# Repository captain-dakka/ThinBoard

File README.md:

# ThinBoard
A thin, low-profile mechnical keyboard. Uses Kailh Choc switches.

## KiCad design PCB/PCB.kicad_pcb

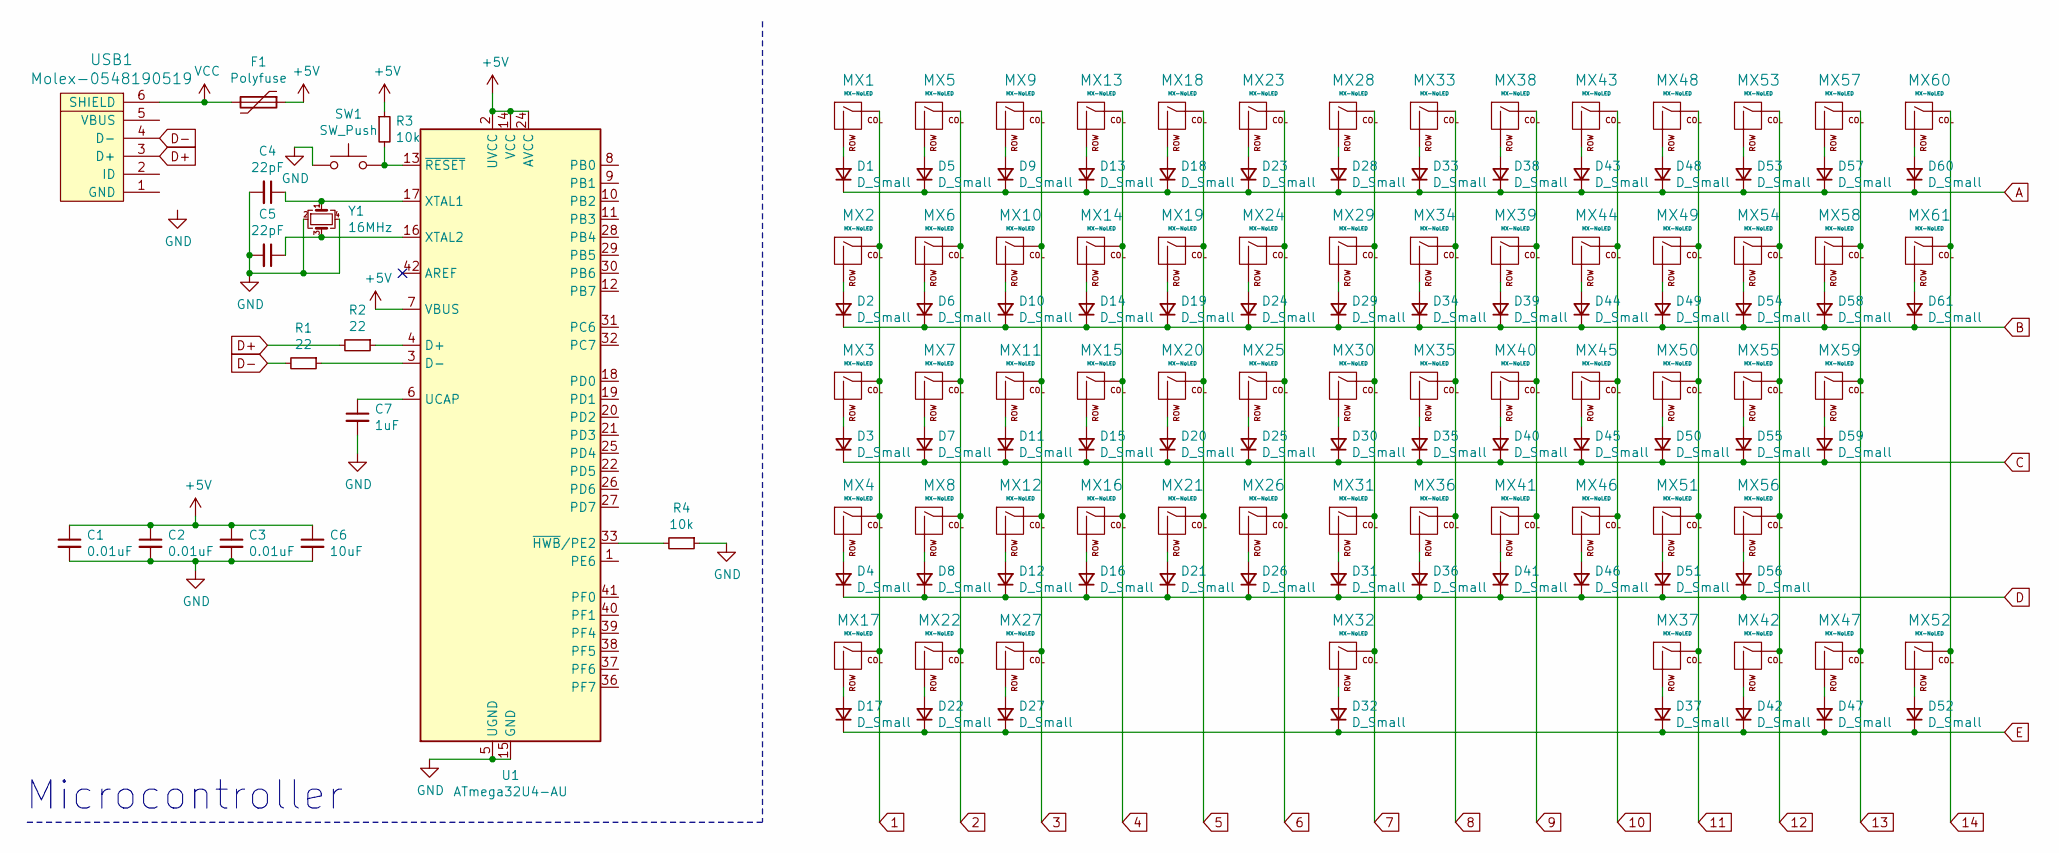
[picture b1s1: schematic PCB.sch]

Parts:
C1, C2, C3: 0.01uF; C_0805_2012Metric
C4, C5: 22pF; C_0805_2012Metric
C6: 10uF; C_0805_2012Metric
C7: 1uF; C_0805_2012Metric
D1, D2, D3, D4, D5, D6, D7, D8, D9, D10, D11, D12, D13, D14, D15, D16, D17, D18, D19, D20, D21, D22, D23, D24, D25, D26, D27, D28, D29, D30, D31, D32, D33, D34, D35, D36, D37, D38, D39, D40, D41, D42, D43, D44, D45, D46, D47, D48, D49, D50, D51, D52, D53, D54, D55, D56, D57, D58, D59, D60, D61: D_Small; D_SOD-123
F1: Polyfuse; Fuse_1206_3216Metric
MX1, MX5, MX6, MX7, MX8, MX9, MX10, MX11, MX12, MX13, MX14, MX15, MX16, MX18, MX19, MX20, MX21, MX23, MX24, MX25, MX26, MX28, MX29, MX30, MX31, MX33, MX34, MX35, MX36, MX38, MX39, MX40, MX41, MX43, MX44, MX45, MX46, MX48, MX49, MX50, MX51, MX53, MX54, MX55, MX57, MX58: MX-NoLED; SW_Kailh_Choc_V1_1.00u
MX2, MX61: MX-NoLED; SW_Kailh_Choc_V1_1.50u
MX3: MX-NoLED; SW_Kailh_Choc_V1_1.75u
MX4, MX59: MX-NoLED; SW_Kailh_Choc_V1_2.25u
MX17, MX22, MX27, MX37, MX42, MX47, MX52: MX-NoLED; SW_Kailh_Choc_V1_1.25u
MX32: MX-NoLED; SW_Kailh_Choc_V1_6.25u
MX56: MX-NoLED; SW_Kailh_Choc_V1_2.75u
MX60: MX-NoLED; SW_Kailh_Choc_V1_2.00u
R1, R2: 22; R_0805_2012Metric
R3, R4: 10k; R_0805_2012Metric
SW1: SW_Push; SKQG-1155865
U1: ATmega32U4-AU; TQFP-44_10x10mm_P0.8mm
USB1: Molex-0548190519; Molex-0548190589
Y1: 16MHz; Crystal_SMD_3225-4Pin_3.2x2.5mm

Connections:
1: MX1.1 (COL), MX2.1 (COL), MX3.1 (COL), MX4.1 (COL), MX17.1 (COL)
2: MX5.1 (COL), MX6.1 (COL), MX7.1 (COL), MX8.1 (COL), MX22.1 (COL)
3: MX9.1 (COL), MX10.1 (COL), MX11.1 (COL), MX12.1 (COL), MX27.1 (COL)
4: MX13.1 (COL), MX14.1 (COL), MX15.1 (COL), MX16.1 (COL)
5: MX18.1 (COL), MX19.1 (COL), MX20.1 (COL), MX21.1 (COL)
6: MX23.1 (COL), MX24.1 (COL), MX25.1 (COL), MX26.1 (COL)
7: MX28.1 (COL), MX29.1 (COL), MX30.1 (COL), MX31.1 (COL), MX32.1 (COL)
8: MX33.1 (COL), MX34.1 (COL), MX35.1 (COL), MX36.1 (COL)
9: MX38.1 (COL), MX39.1 (COL), MX40.1 (COL), MX41.1 (COL)
10: MX43.1 (COL), MX44.1 (COL), MX45.1 (COL), MX46.1 (COL)
11: MX37.1 (COL), MX48.1 (COL), MX49.1 (COL), MX50.1 (COL), MX51.1 (COL)
12: MX42.1 (COL), MX53.1 (COL), MX54.1 (COL), MX55.1 (COL), MX56.1 (COL)
13: MX47.1 (COL), MX57.1 (COL), MX58.1 (COL), MX59.1 (COL)
14: MX52.1 (COL), MX60.1 (COL), MX61.1 (COL)
+5V: C1.1, C2.1, C3.1, C6.1, F1.1, R3.1, U1.2 (UVCC), U1.7 (VBUS), U1.14 (VCC), U1.24 (AVCC), U1.34 (VCC), U1.44 (AVCC)
A: D1.1 (K), D5.1 (K), D9.1 (K), D13.1 (K), D18.1 (K), D23.1 (K), D28.1 (K), D33.1 (K), D38.1 (K), D43.1 (K), D48.1 (K), D53.1 (K), D57.1 (K), D60.1 (K)
B: D2.1 (K), D6.1 (K), D10.1 (K), D14.1 (K), D19.1 (K), D24.1 (K), D29.1 (K), D34.1 (K), D39.1 (K), D44.1 (K), D49.1 (K), D54.1 (K), D58.1 (K), D61.1 (K)
C: D3.1 (K), D7.1 (K), D11.1 (K), D15.1 (K), D20.1 (K), D25.1 (K), D30.1 (K), D35.1 (K), D40.1 (K), D45.1 (K), D50.1 (K), D55.1 (K), D59.1 (K)
D: D4.1 (K), D8.1 (K), D12.1 (K), D16.1 (K), D21.1 (K), D26.1 (K), D31.1 (K), D36.1 (K), D41.1 (K), D46.1 (K), D51.1 (K), D56.1 (K)
D+: R2.2, USB1.3 (D+)
D-: R1.2, USB1.4 (D-)
E: D17.1 (K), D22.1 (K), D27.1 (K), D32.1 (K), D37.1 (K), D42.1 (K), D47.1 (K), D52.1 (K)
GND: C1.2, C2.2, C3.2, C4.2, C5.2, C6.2, C7.2, R4.1, SW1.1, U1.5 (UGND), U1.15 (GND), U1.23 (GND), U1.35 (GND), U1.43 (GND), Y1.2, Y1.4
unnamed: C4.1, U1.17 (XTAL1), Y1.1
unnamed: C5.1, U1.16 (XTAL2), Y1.3
unnamed: C7.1, U1.6 (UCAP)
unnamed: D1.2 (A), MX1.2 (ROW)
unnamed: D2.2 (A), MX2.2 (ROW)
unnamed: D3.2 (A), MX3.2 (ROW)
unnamed: D4.2 (A), MX4.2 (ROW)
unnamed: D5.2 (A), MX5.2 (ROW)
unnamed: D6.2 (A), MX6.2 (ROW)
unnamed: D7.2 (A), MX7.2 (ROW)
unnamed: D8.2 (A), MX8.2 (ROW)
unnamed: D9.2 (A), MX9.2 (ROW)
unnamed: D10.2 (A), MX10.2 (ROW)
unnamed: D11.2 (A), MX11.2 (ROW)
unnamed: D12.2 (A), MX12.2 (ROW)
unnamed: D13.2 (A), MX13.2 (ROW)
unnamed: D14.2 (A), MX14.2 (ROW)
unnamed: D15.2 (A), MX15.2 (ROW)
unnamed: D16.2 (A), MX16.2 (ROW)
unnamed: D17.2 (A), MX17.2 (ROW)
unnamed: D18.2 (A), MX18.2 (ROW)
unnamed: D19.2 (A), MX19.2 (ROW)
unnamed: D20.2 (A), MX20.2 (ROW)
unnamed: D21.2 (A), MX21.2 (ROW)
unnamed: D22.2 (A), MX22.2 (ROW)
unnamed: D23.2 (A), MX23.2 (ROW)
unnamed: D24.2 (A), MX24.2 (ROW)
unnamed: D25.2 (A), MX25.2 (ROW)
unnamed: D26.2 (A), MX26.2 (ROW)
unnamed: D27.2 (A), MX27.2 (ROW)
unnamed: D28.2 (A), MX28.2 (ROW)
unnamed: D29.2 (A), MX29.2 (ROW)
unnamed: D30.2 (A), MX30.2 (ROW)
unnamed: D31.2 (A), MX31.2 (ROW)
unnamed: D32.2 (A), MX32.2 (ROW)
unnamed: D33.2 (A), MX33.2 (ROW)
unnamed: D34.2 (A), MX34.2 (ROW)
unnamed: D35.2 (A), MX35.2 (ROW)
unnamed: D36.2 (A), MX36.2 (ROW)
unnamed: D37.2 (A), MX37.2 (ROW)
unnamed: D38.2 (A), MX38.2 (ROW)
unnamed: D39.2 (A), MX39.2 (ROW)
unnamed: D40.2 (A), MX40.2 (ROW)
unnamed: D41.2 (A), MX41.2 (ROW)
unnamed: D42.2 (A), MX42.2 (ROW)
unnamed: D43.2 (A), MX43.2 (ROW)
unnamed: D44.2 (A), MX44.2 (ROW)
unnamed: D45.2 (A), MX45.2 (ROW)
unnamed: D46.2 (A), MX46.2 (ROW)
unnamed: D47.2 (A), MX47.2 (ROW)
unnamed: D48.2 (A), MX48.2 (ROW)
unnamed: D49.2 (A), MX49.2 (ROW)
unnamed: D50.2 (A), MX50.2 (ROW)
unnamed: D51.2 (A), MX51.2 (ROW)
unnamed: D52.2 (A), MX52.2 (ROW)
unnamed: D53.2 (A), MX53.2 (ROW)
unnamed: D54.2 (A), MX54.2 (ROW)
unnamed: D55.2 (A), MX55.2 (ROW)
unnamed: D56.2 (A), MX56.2 (ROW)
unnamed: D57.2 (A), MX57.2 (ROW)
unnamed: D58.2 (A), MX58.2 (ROW)
unnamed: D59.2 (A), MX59.2 (ROW)
unnamed: D60.2 (A), MX60.2 (ROW)
unnamed: D61.2 (A), MX61.2 (ROW)
unnamed: R1.1, U1.3 (D-)
unnamed: R2.1, U1.4 (D+)
unnamed: R3.2, SW1.2, U1.13 (~RESET)
unnamed: R4.2, U1.33 (~HWB~/PE2)
VCC: F1.2, USB1.6 (SHIELD)

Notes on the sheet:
Microcontroller

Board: 2 copper layers, 138 parts (0 on the bottom side), 92 nets, no tracks yet.

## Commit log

2021-05-11 Initalising KiCad project
2021-05-11 Adding KiCad footprints.
2021-05-11 Completed MCU zone of schematic.
2021-05-11 Shutting down for the night, got first switch down
2021-05-12 Changing KiCad project directory and names of files.
2021-05-12 Adding keys to schematic, and giving components footprints.
2021-05-12 Revert "Changing KiCad project directory and names of files."
    This reverts commit 86f4d9342d508a4dbac61b5936f348f8df2db9b5.
2021-05-12 Started work on pcb layout, currently adding in proper key sizes.
2021-05-15 Restarted work on key placement using new footprint.
